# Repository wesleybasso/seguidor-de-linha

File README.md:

# PEGASUS Rev A0

PEGASUS e um robo seguidor de linha modular em tres placas.

- `HDB-001` Brain Board: Black Pill STM32F411, XIAO ESP32-S3/Plus, debug e conectores para o chassi.
- `HDB-100` Chassis / Power Board: LiPo 2S, chave, TB6612FNG, buck 5V, motores e succao central.
- `HDB-101` Sensor Board: placa frontal/adaptadora para sensor vermelho de 8 canais na Rev A0.

## Estrutura

- `kicad documents/`: projetos KiCad e biblioteca local de footprints placeholder.
- `docs/`: requisitos, pinagem e decisoes de engenharia.
- `firmware/`: requisitos iniciais de firmware STM32/ESP32 e protocolo UART.
- `manufacturing/`: checklist preliminar JLCPCB/PCBWay.
- `sketches/`: desenhos de arquitetura e mecanica.

## Estado Atual

Base mecanica KiCad Rev A0 criada. Ainda nao ha roteamento final, ERC/DRC final, nem Gerbers de fabricacao.

Nao enviar para fabricacao sem revisar:

- footprints reais com paquimetro;
- pinagem real da Black Pill, XIAO e modulo TB6612;
- corrente dos motores e succao;
- espacamento de bateria, motores, ventosa e empilhamento;
- DRC/ERC completo apos esquematicos e roteamento.

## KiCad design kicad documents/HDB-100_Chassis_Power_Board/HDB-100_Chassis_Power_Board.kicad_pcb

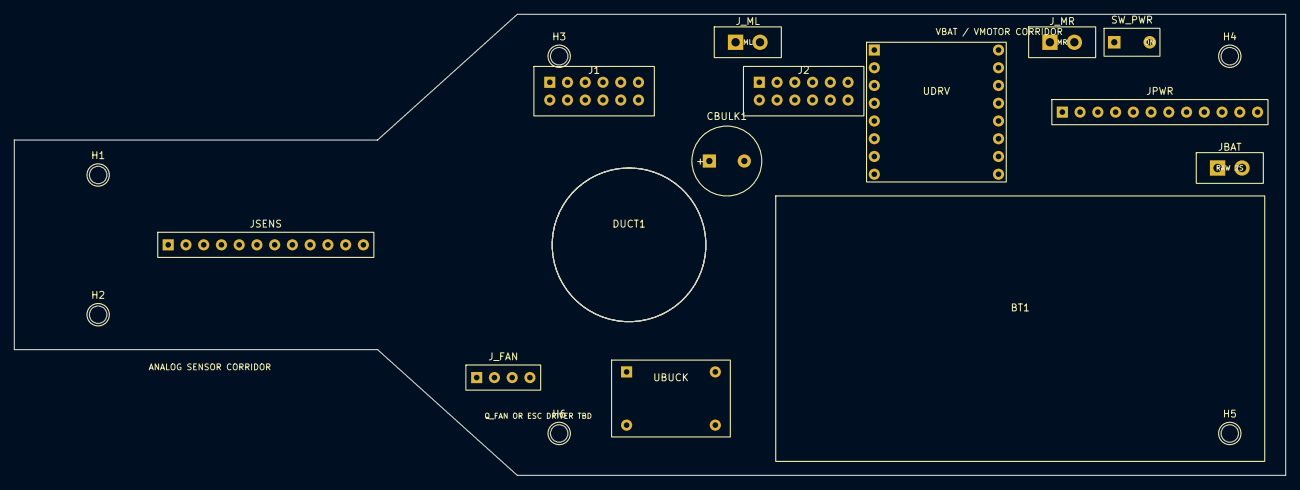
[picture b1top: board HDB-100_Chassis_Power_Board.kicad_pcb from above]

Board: 2 copper layers, 182.0 x 66.0 mm, 20 parts (0 on the bottom side), 28 nets, no tracks yet.

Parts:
BT1: LiPo 2S 70x38x18; LiPo_2S_Battery_70x38
CBULK1: 470-1000uF placeholder; BulkCap_Radial_D10_P5
DUCT1: Suction duct D22; Suction_Hole_D22
H1, H2, H3, H4, H5, H6: M2.5; MountingHole_2p5_NPTH
J1: B2B Sensors/Logic; B2B_2x6_2p54
J2: B2B Commands/Power; B2B_2x6_2p54
JBAT: XT30 LiPo 2S placeholder; PowerConnector_1x02_3p5
JPWR: Power IO placeholder; PinHeader_1x12_2p54
JSENS: Sensor Board; PinHeader_1x12_2p54
J_FAN: Fan/ESC placeholder; PinHeader_1x04_2p54
J_ML: Motor L placeholder; PowerConnector_1x02_3p5
J_MR: Motor R placeholder; PowerConnector_1x02_3p5
SW_PWR: Power switch placeholder; SlideSwitch_SPST_8x4
UBUCK: Mini360 5V buck; Mini360_Buck_17x11
UDRV: TB6612FNG module TBD pinout; TB6612_Module_20x20

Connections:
3V3: J1.1, JSENS.1
5V_IN: J2.3, JPWR.3, J_FAN.4, UBUCK.3, UDRV.12
A0: J1.3, JSENS.3
A1: J1.4, JSENS.4
A2: J1.5, JSENS.5
A3: J1.6, JSENS.6
A4: J1.7, JSENS.7
A5: J1.8, JSENS.8
A6: J1.9, JSENS.9
A7: J1.10, JSENS.10
AIN1: J2.6, UDRV.2
AIN2: J2.7, UDRV.3
AOUT1: JPWR.5, J_ML.1, UDRV.7
AOUT2: JPWR.6, J_ML.2, UDRV.8
BIN1: J2.9, UDRV.14
BIN2: J2.10, UDRV.13
BOUT1: JPWR.7, J_MR.1, UDRV.10
BOUT2: JPWR.8, J_MR.2, UDRV.9
FAN_PWM: J2.12, JPWR.9, J_FAN.3
GND: CBULK1.2, J1.2, J2.2, J2.4, JBAT.2, JPWR.2, JPWR.4, JPWR.10, JSENS.2, J_FAN.2, UBUCK.2, UBUCK.4, UDRV.6, UDRV.11
LAT_L: J1.11, JSENS.11
LAT_R: J1.12, JSENS.12
PWMA: J2.5, UDRV.1
PWMB: J2.8, UDRV.15
STBY: J2.11, UDRV.4
VBAT_ADC: J2.1, JPWR.12
VBAT_RAW: JBAT.1, SW_PWR.1
VMOTOR: CBULK1.1, JPWR.1, JPWR.11, J_FAN.1, SW_PWR.2, UBUCK.1, UDRV.5, UDRV.16

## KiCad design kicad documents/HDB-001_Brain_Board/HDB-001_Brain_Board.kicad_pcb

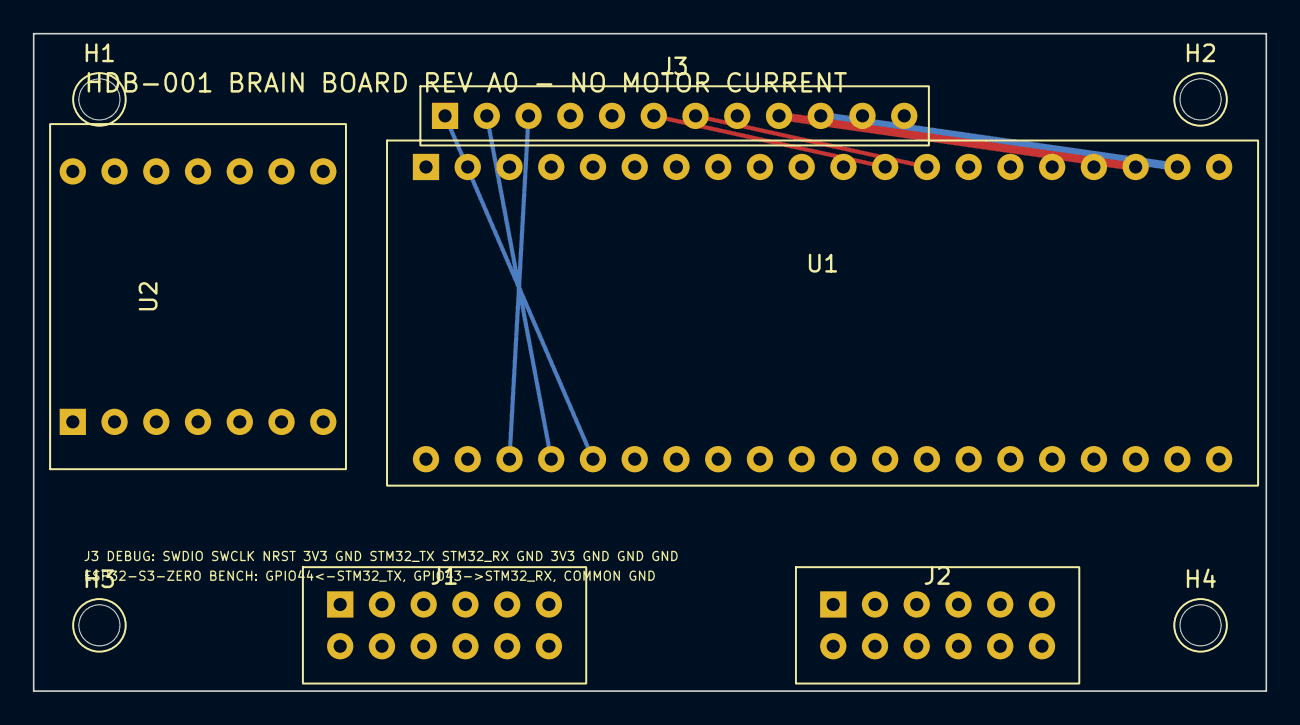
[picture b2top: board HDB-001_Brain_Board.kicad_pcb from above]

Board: 2 copper layers, 75.0 x 40.0 mm, 9 parts (0 on the bottom side), 25 nets.

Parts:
H1, H2, H3, H4: M2.5; MountingHole_2p5_NPTH
J1: B2B Sensors/Logic; B2B_2x6_2p54
J2: B2B Commands/Power; B2B_2x6_2p54
J3: SWD/UART/Status placeholder; PinHeader_1x12_2p54
U1: Black Pill STM32F411CEU6; BlackPill_STM32F411_53x21
U2: XIAO ESP32-S3/Plus TBD; XIAO_ESP32S3_21x18

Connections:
3V3: J1.1, J3.4, J3.9, U1.18, U1.22
A0: J1.3, U1.3
A1: J1.4, U1.4
A2: J1.5, U1.5
A3: J1.6, U1.6
A4: J1.7, U1.7
A5: J1.8, U1.8
A6: J1.9, U1.9
A7: J1.10, U1.10
AIN1: J2.6, U1.25
AIN2: J2.7, U1.26
BIN1: J2.9, U1.27
BIN2: J2.10, U1.28
FAN_PWM: J2.12, U1.11
GND: J1.2, J2.2, J2.4, J3.5, J3.8, J3.10, J3.11, J3.12, U1.19, U1.21
LAT_L: J1.11, U1.30
LAT_R: J1.12, U1.31
NRST: J3.3, U1.38
PWMA: J2.5, U1.23
PWMB: J2.8, U1.24
STBY: J2.11, U1.29
STM32_RX: J3.7, U1.13
STM32_TX: J3.6, U1.12
SWCLK: J3.2, U1.37
SWDIO: J3.1, U1.36

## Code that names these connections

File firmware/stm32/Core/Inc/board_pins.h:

#pragma once

/*
 * PEGASUS Rev A0 logical pin map from docs/HPS-001.
 * Configure the real STM32Cube GPIO/ADC/TIM instances to match these signals.
 *
 * Sensors:
 *   A0..A7  -> PA0..PA7
 *   LAT_L   -> PB0
 *   LAT_R   -> PB1
 *
 * TB6612:
 *   PWMA -> PB8
 *   PWMB -> PB9
 *   AIN1 -> PB10
 *   AIN2 -> PB11
 *   BIN1 -> PB12
 *   BIN2 -> PB13
 *   STBY -> PB14
 *
 * Fan:
 *   FAN_PWM -> PA8
 *
 * UART to ESP32:
 *   STM32_TX -> PA9
 *   STM32_RX -> PA10
 */

#define PEGASUS_SENSOR_FRONT_COUNT 8u
#define PEGASUS_SENSOR_TOTAL_COUNT 10u
#define PEGASUS_PWM_MAX 1000
#define PEGASUS_CONTROL_HZ 500u
#define PEGASUS_TELEMETRY_HZ 25u
